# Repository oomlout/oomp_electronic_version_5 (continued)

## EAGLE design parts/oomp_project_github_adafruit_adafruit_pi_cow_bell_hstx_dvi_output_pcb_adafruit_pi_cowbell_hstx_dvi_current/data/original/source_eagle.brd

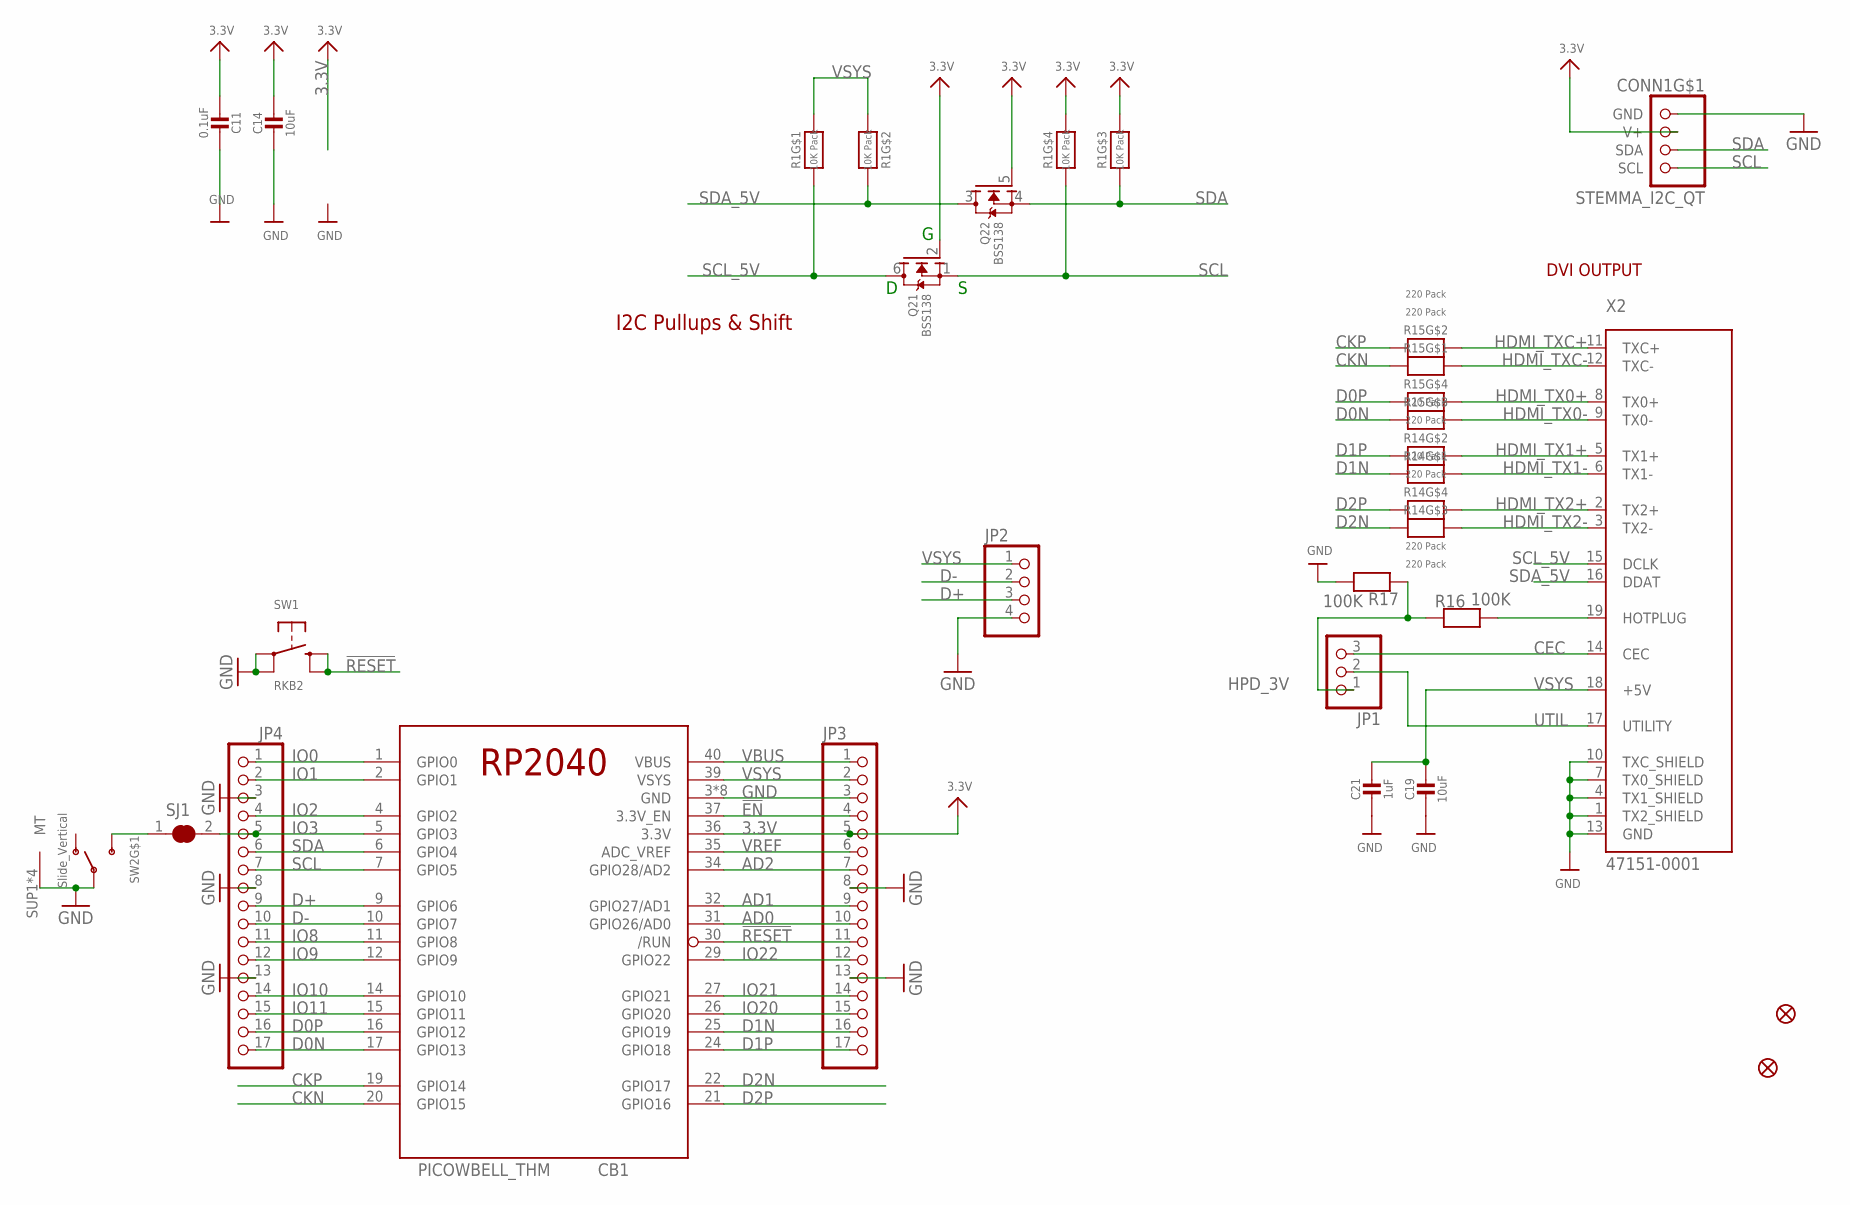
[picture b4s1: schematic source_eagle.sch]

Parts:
C11: 0.1uF; 0603-NO
C14, C19: 10uF; 0805-NO
C21: 1uF; 0603-NO
CB1: PICOWBELL_THM
CONN1: STEMMA_I2C_QT; JST_SH4
FID1, FID2: FIDUCIAL_1MM
JP1: HEADER-1X3ROUND; 1X03_ROUND
JP2: HEADER-1X4ROUND; 1X04_ROUND
JP3, JP4: HEADER-1X17; 1X17_ROUND70
Q2: BSS138; SOT363
R1: 10K Pack; RESPACK_4X0603
R14, R15: 220 Pack; RESPACK_4X0603
R16, R17: 100K; 0603-NO
SJ1: SOLDERJUMPER_CLOSED; SOLDERJUMPER_CLOSEDWIRE
SW1: RKB2; BTN_RKB2_4.6X2.8
SW2: Slide_Vertical; SPDT_SMT_SSSS811101
X2: 47151-0001; MINIHDMI_CNCTECH

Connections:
3.3V: C11.2, C14.1, CB1.36 (3.3V), CONN1.2 (V+), JP3.5, Q2.2 (G), Q2.5 (G), R1.5 (2), R1.6 (2)
!EN: CB1.37 (3.3V_EN), JP3.4
!RESET: CB1.30 (/RUN), JP3.11, SW1.B (S), SW1.B' (S1)
AD0: CB1.31 (GPIO26/AD0), JP3.10
AD1: CB1.32 (GPIO27/AD1), JP3.9
AD2: CB1.34 (GPIO28/AD2), JP3.7
CEC: JP1.3, X2.14 (CEC)
CKN: CB1.20 (GPIO15), R15.8 (2)
CKP: CB1.19 (GPIO14), R15.7 (2)
D0N: CB1.17 (GPIO13), JP4.17, R15.6 (2)
D0P: CB1.16 (GPIO12), JP4.16, R15.5 (2)
D1N: CB1.25 (GPIO19), JP3.16, R14.8 (2)
D1P: CB1.24 (GPIO18), JP3.17, R14.7 (2)
D2N: CB1.22 (GPIO17), R14.6 (2)
D2P: CB1.21 (GPIO16), R14.5 (2)
D+: CB1.9 (GPIO6), JP2.3, JP4.9
D-: CB1.10 (GPIO7), JP2.2, JP4.10
GND: C11.1, C14.2, C19.2, C21.2, CB1.3 (GND), CB1.8 (GND), CB1.13 (GND), CB1.18 (GND), CB1.23 (GND), CB1.28 (GND), CB1.33 (GND), CB1.38 (GND), CONN1.1 (GND), JP2.4, JP3.3, JP3.8, JP3.13, JP4.3, JP4.8, JP4.13, R17.2, SW1.A, SW1.A' (P1), SW2.B, SW2.SUP1 (MT), SW2.SUP2 (MT), SW2.SUP3 (MT), SW2.SUP4 (MT), X2.1 (TX2_SHIELD), X2.4 (TX1_SHIELD), X2.7 (TX0_SHIELD), X2.10 (TXC_SHIELD), X2.13 (GND), X2.MNT1 (GND), X2.MNT2 (GND), X2.MNT3 (GND), X2.MNT4 (GND)
HDMI_TX0+: R15.4 (1), X2.8 (TX0+)
HDMI_TX0-: R15.3 (1), X2.9 (TX0-)
HDMI_TX1+: R14.2 (1), X2.5 (TX1+)
HDMI_TX1-: R14.1, X2.6 (TX1-)
HDMI_TX2+: R14.4 (1), X2.2 (TX2+)
HDMI_TX2-: R14.3 (1), X2.3 (TX2-)
HDMI_TXC+: R15.2 (1), X2.11 (TXC+)
HDMI_TXC-: R15.1, X2.12 (TXC-)
HPD: R16.2, X2.19 (HOTPLUG)
HPD_3V: JP1.1, R16.1, R17.1
IO0: CB1.1 (GPIO0), JP4.1
IO1: CB1.2 (GPIO1), JP4.2
IO2: CB1.4 (GPIO2), JP4.4
IO3: CB1.5 (GPIO3), JP4.5, SJ1.2
IO8: CB1.11 (GPIO8), JP4.11
IO9: CB1.12 (GPIO9), JP4.12
IO10: CB1.14 (GPIO10), JP4.14
IO11: CB1.15 (GPIO11), JP4.15
IO20: CB1.26 (GPIO20), JP3.15
IO21: CB1.27 (GPIO21), JP3.14
IO22: CB1.29 (GPIO22), JP3.12
unnamed: SJ1.1, SW2.C (S)
SCL: CB1.7 (GPIO5), CONN1.4 (SCL), JP4.7, Q2.1 (S), R1.4 (1)
SCL_5V: Q2.6 (D), R1.8 (2), X2.15 (DCLK)
SDA: CB1.6 (GPIO4), CONN1.3 (SDA), JP4.6, Q2.4 (S), R1.3 (1)
SDA_5V: Q2.3 (D), R1.7 (2), X2.16 (DDAT)
UTIL: JP1.2, X2.17 (UTILITY)
VBUS: CB1.40 (VBUS), JP3.1
VREF: CB1.35 (ADC_VREF), JP3.6
VSYS: C19.1, C21.1, CB1.39 (VSYS), JP2.1, JP3.2, R1.1, R1.2 (1), X2.18 (+5V)

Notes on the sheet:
DVI OUTPUT
I2C Pullups & Shift

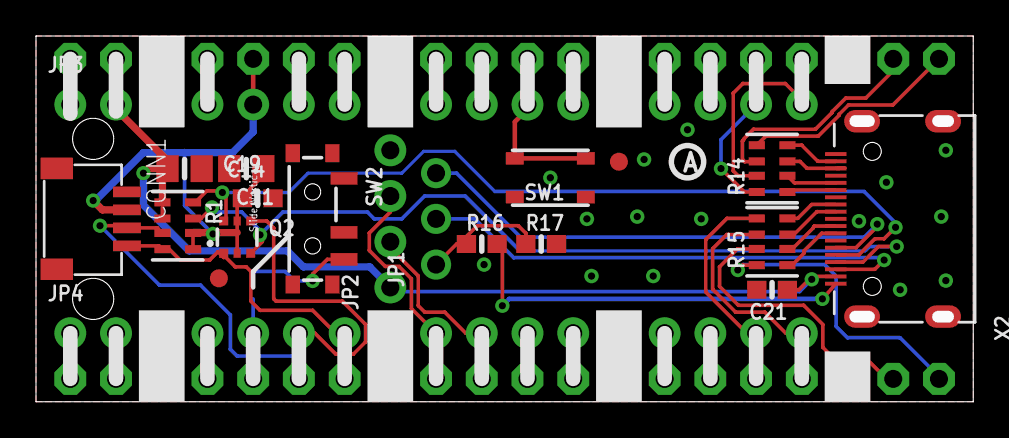
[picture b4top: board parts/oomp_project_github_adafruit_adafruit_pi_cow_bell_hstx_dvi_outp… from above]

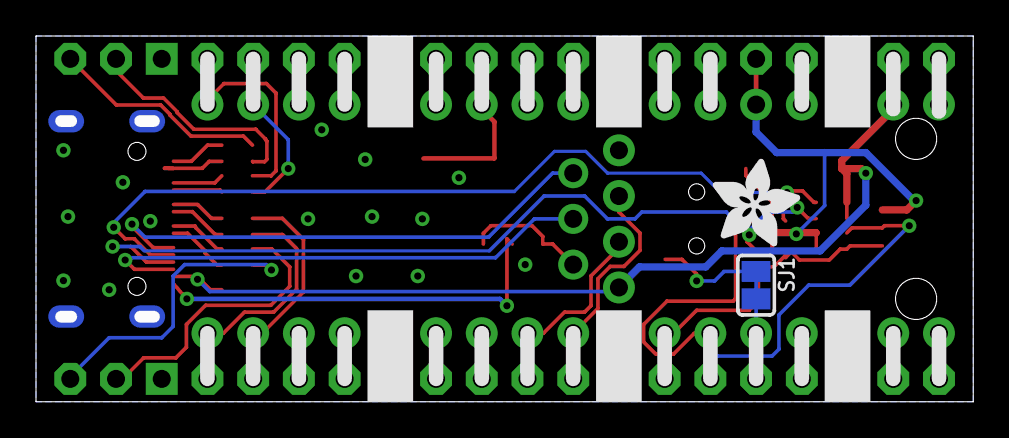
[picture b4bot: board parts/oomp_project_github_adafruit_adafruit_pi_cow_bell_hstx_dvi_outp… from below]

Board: 2 copper layers, 52.1 x 20.3 mm, 108 parts (44 on the bottom side), 48 nets.

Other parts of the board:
PLABEL109: PLABEL109
PLABEL110: PLABEL110
PLABEL111: PLABEL111
PLABEL112: PLABEL112
PLABEL113: PLABEL113
PLABEL114: PLABEL114
PLABEL115: PLABEL115
PLABEL116: PLABEL116
PLABEL117: PLABEL117
PLABEL118: PLABEL118
PLABEL119: PLABEL119
PLABEL120: PLABEL120
PLABEL121: PLABEL121
PLABEL122: PLABEL122
PLABEL123: PLABEL123
PLABEL124: PLABEL124
PLABEL125: PLABEL125
PLABEL126: PLABEL126
PLABEL127: PLABEL127
PLABEL128: PLABEL128
PLABEL129: PLABEL129
PLABEL130: PLABEL130
PLABEL131: PLABEL131
PLABEL132: PLABEL132
PLABEL133: PLABEL133
PLABEL134: PLABEL134
PLABEL135: PLABEL135
PLABEL136: PLABEL136
PLABEL137: PLABEL137
PLABEL138: PLABEL138
PLABEL139: PLABEL139
PLABEL140: PLABEL140
PLABEL141: PLABEL141
PLABEL142: PLABEL142
PLABEL143: PLABEL143
PLABEL144: PLABEL144
PLABEL145: PLABEL145
PLABEL146: PLABEL146
PLABEL147: PLABEL147
PLABEL148: PLABEL148
PLABEL149: PLABEL149
PLABEL150: PLABEL150
PLABEL151: PLABEL151
PLABEL152: PLABEL152
PLABEL154: PLABEL154
PLABEL155: PLABEL155
PLABEL156: PLABEL156
PLABEL157: PLABEL157
PLABEL158: PLABEL158
PLABEL159: PLABEL159
PLABEL160: PLABEL160
PLABEL161: PLABEL161
PLABEL162: PLABEL162
PLABEL163: PLABEL163
PLABEL164: PLABEL164
PLABEL165: PLABEL165
PLABEL166: PLABEL166
PLABEL167: PLABEL167
PLABEL168: PLABEL168
PLABEL169: PLABEL169
PLABEL170: PLABEL170
PLABEL171: PLABEL171
PLABEL172: PLABEL172
PLABEL173: PLABEL173
PLABEL174: PLABEL174
PLABEL175: PLABEL175
PLABEL176: PLABEL176
PLABEL177: PLABEL177
PLABEL178: PLABEL178
PLABEL179: PLABEL179
PLABEL180: PLABEL180
PLABEL181: PLABEL181
PLABEL182: PLABEL182
PLABEL183: PLABEL183
PLABEL184: PLABEL184
PLABEL185: PLABEL185
PLABEL186: PLABEL186
PLABEL187: PLABEL187
PLABEL188: PLABEL188
PLABEL189: PLABEL189
PLABEL190: PLABEL190
PLABEL191: PLABEL191
PLABEL192: PLABEL192
PLABEL193: PLABEL193
U$1: ADAFRUIT_5MM
U$10: PCBFEAT-REV-040

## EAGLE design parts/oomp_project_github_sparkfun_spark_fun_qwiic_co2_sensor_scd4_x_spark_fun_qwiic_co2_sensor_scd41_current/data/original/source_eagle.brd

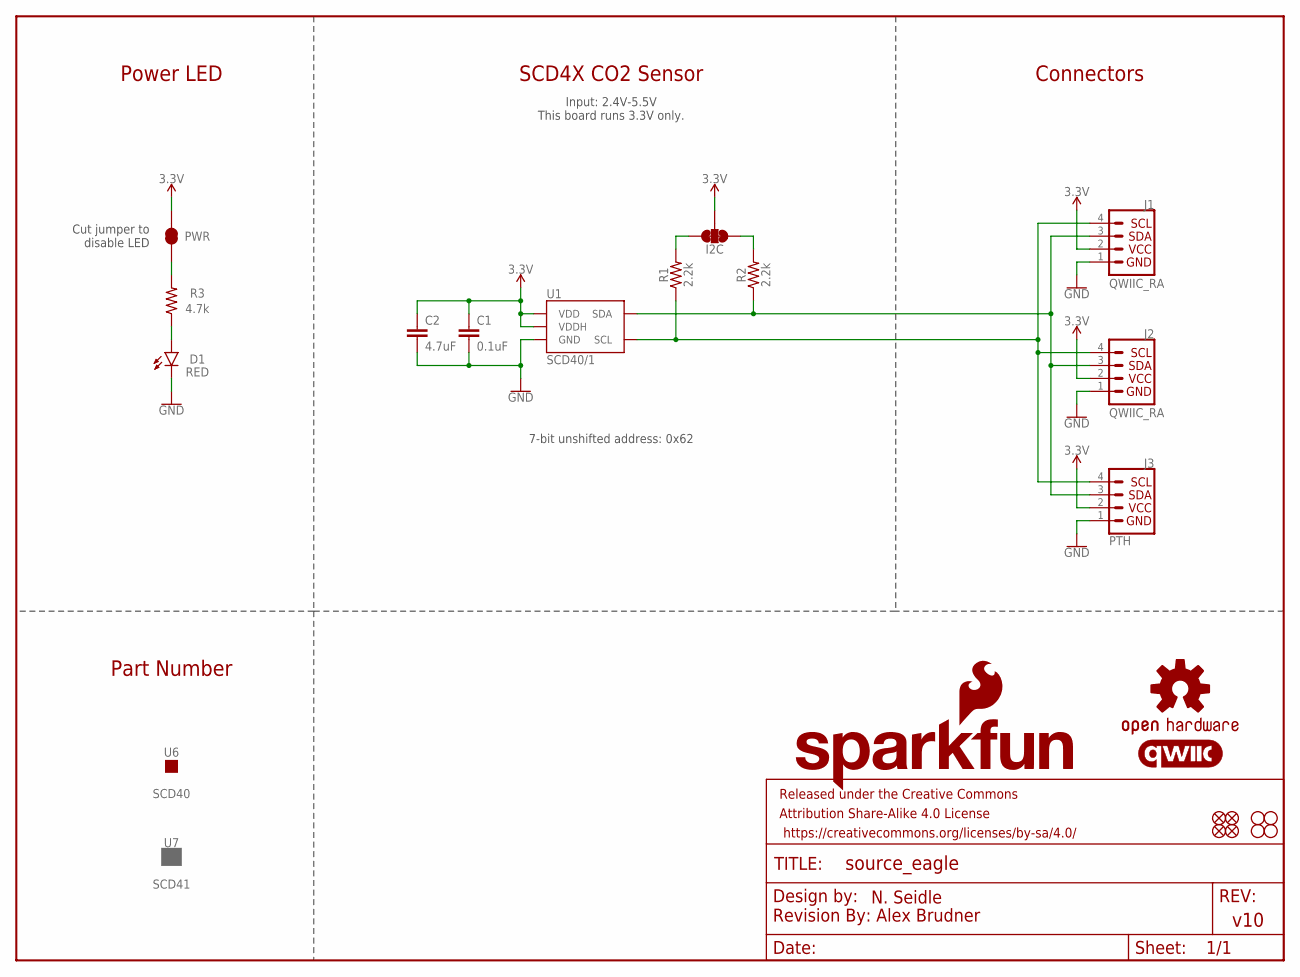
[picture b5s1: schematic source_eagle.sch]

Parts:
C1: 0.1uF; 0603
C2: 4.7uF; 0603
D1: RED; LED-0603
FD1, FD2, FD3, FD4: FIDUCIALUFIDUCIAL; FIDUCIAL-MICRO
FRAME1: FRAME-LETTER; CREATIVE_COMMONS
H1, H2, H3, H4: STAND-OFF
I2C: I2C; SMT-JUMPER_3_2-NC_TRACE_SILK
J1, J2: QWIIC_RA; JST04_1MM_RA
J3: PTH; 1X04_NO_SILK
LOGO1: QWIIC_LOGO_CONNECTOR; QWIIC_5.5MM
LOGO2: OSHW-LOGOS; OSHW-LOGO-S
LOGO3: SFE_LOGO_NAME_FLAMEBLANK; BLANK
PWR: PWR; SMT-JUMPER_2_NC_TRACE_SILK
R1, R2: 2.2k; 0603
R3: 4.7k; 0603
U1: SCD40/1; SCD4X
U6: SCD40; PRODUCT_IDENT_NO_NO-SILK
U7: SCD41; PRODUCT_IDENT_PASTE_NO-SILK

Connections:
3.3V: C1.1, C2.1, I2C.2, J1.2, J2.2, J3.2, PWR.2, U1.7 (VDD), U1.19 (VDDH)
GND: C1.2, C2.2, D1.C, J1.1, J2.1, J3.1, U1.6 (GND), U1.20 (GND), U1.CP (GND)
unnamed: I2C.1, R2.2
unnamed: I2C.3, R1.2
unnamed: PWR.1, R3.2
unnamed: D1.A, R3.1
SCL: J1.4, J2.4, J3.4, R1.1, U1.9 (SCL)
SDA: J1.3, J2.3, J3.3, R2.1, U1.10 (SDA)

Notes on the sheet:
Cut jumper to disable LED
SCD4X CO2 Sensor
Power LED
Connectors
Part Number
Input: 2.4V-5.5V This board runs 3.3V only.
7-bit unshifted address: 0x62

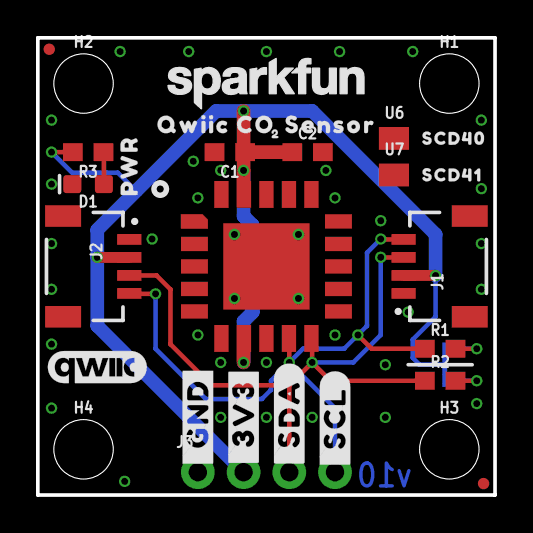
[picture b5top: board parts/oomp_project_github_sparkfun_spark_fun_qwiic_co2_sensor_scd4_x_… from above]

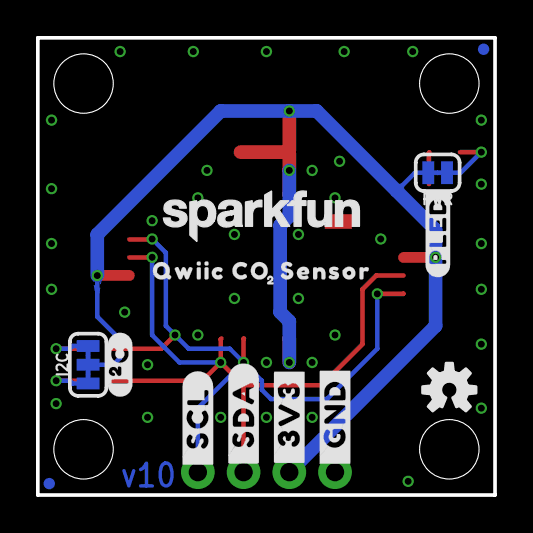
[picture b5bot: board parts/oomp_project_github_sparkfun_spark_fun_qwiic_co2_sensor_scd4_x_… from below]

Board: 2 copper layers, 25.4 x 25.4 mm, 49 parts (16 on the bottom side), 8 nets.

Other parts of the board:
U$1, U$18: #_GND#14
U$2, U$19: #_3V3#15
U$3, U$20: #_SDA#15
U$4, U$21: #_SCL#16
U$5, U$12: SFE_LOGO_NAME_.1
U$6: SCD414140404021
U$7: SCD40414140404022
U$8, U$13: QWIIC_CO0
U$9, U$14: SENSOR0
U$10, U$15: 20
U$11: SFE_LOGO_FLAME_STOP_.1
U$16: #PLED#21
U$17: #I�C#0
U$22: ORDERING_INSTRUCTIONS
U$23: PWR0

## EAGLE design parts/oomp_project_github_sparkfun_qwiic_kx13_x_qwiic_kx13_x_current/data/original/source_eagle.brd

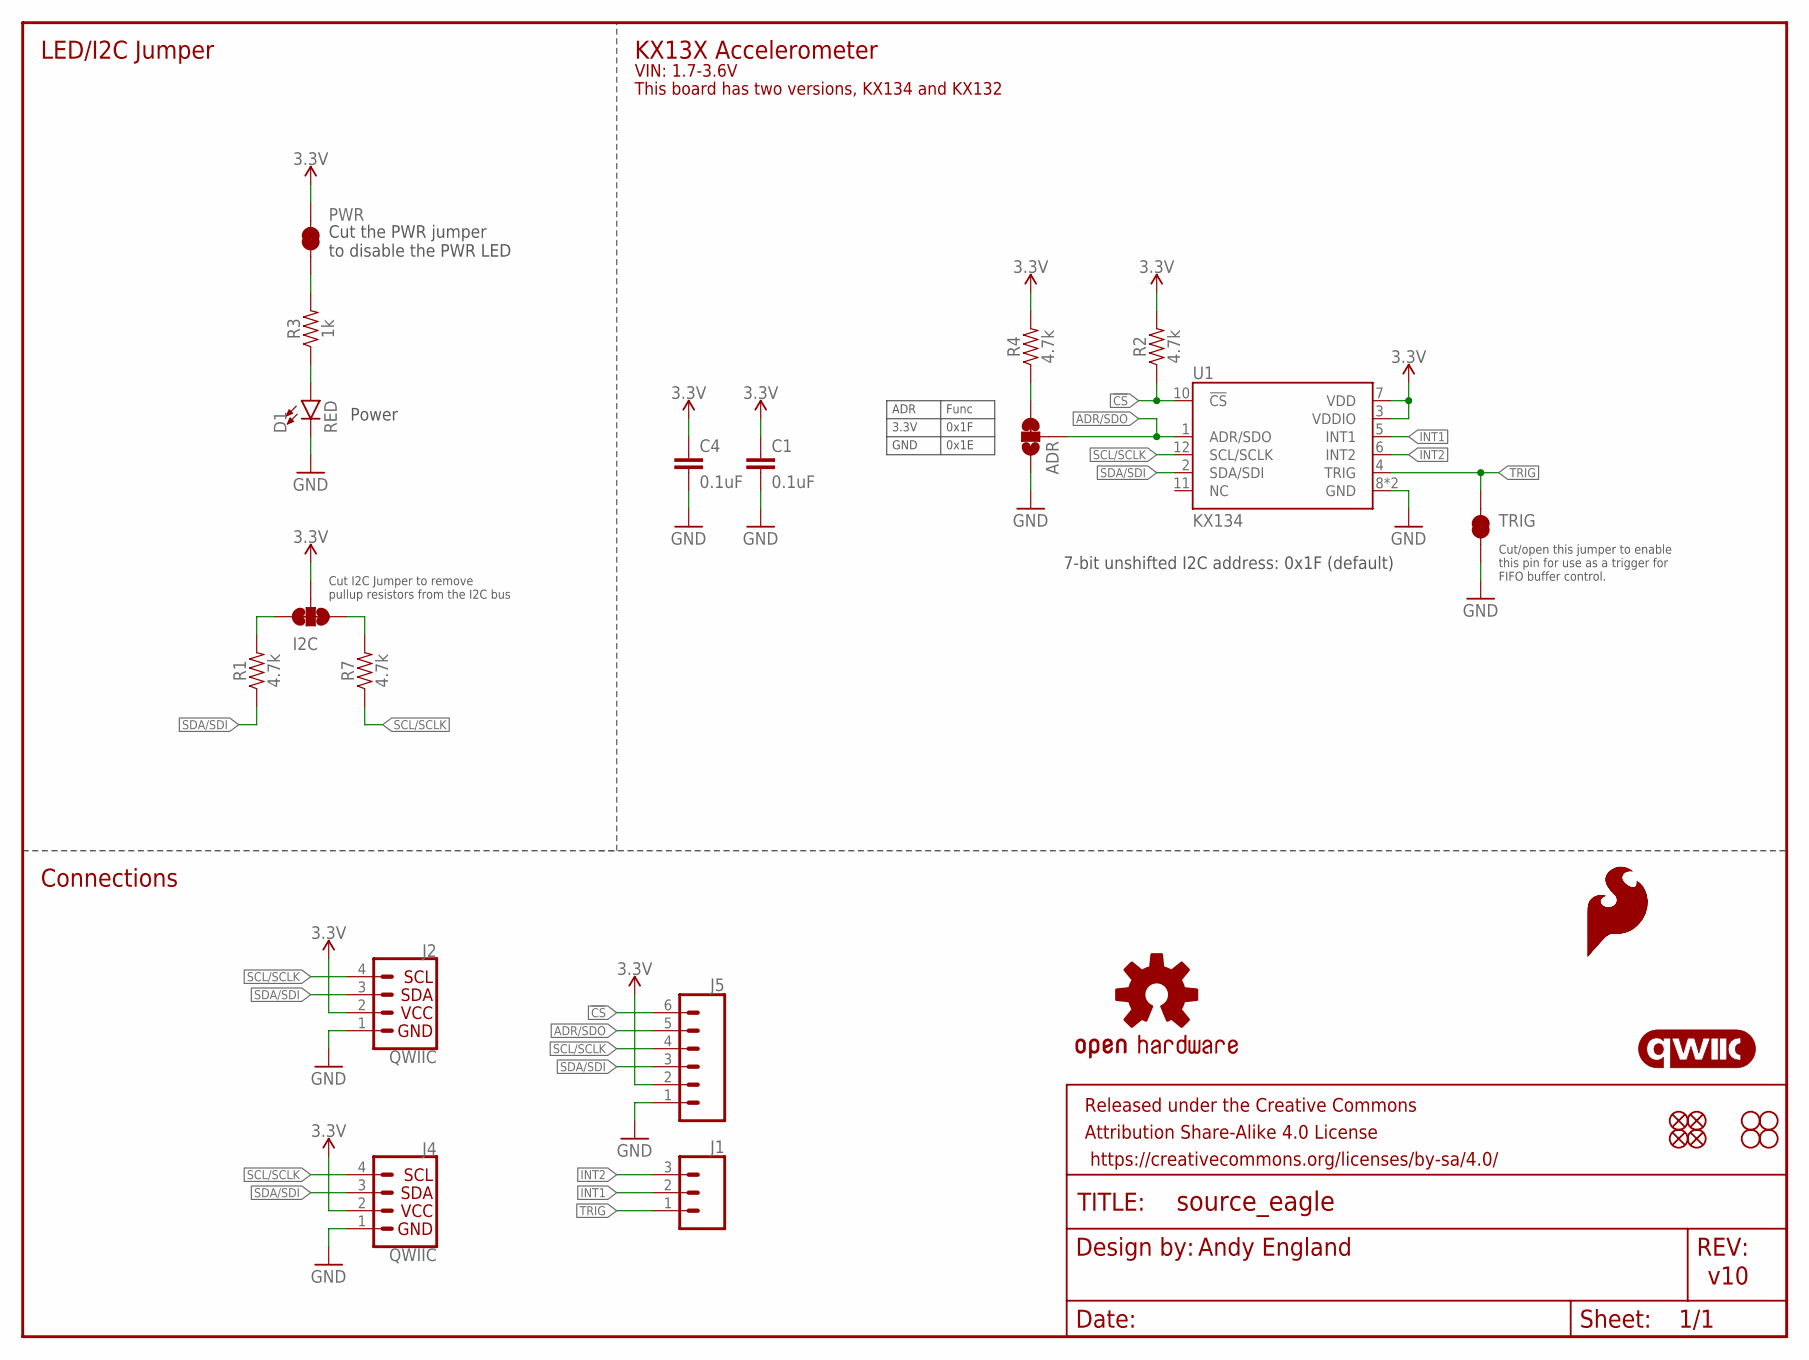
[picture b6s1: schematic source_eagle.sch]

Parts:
ADR: JUMPER-SMT_3_1-NC_TRACE_SILK; SMT-JUMPER_3_1-NC_TRACE_SILK
C1, C4: 0.1uF; 0603
D1: RED; LED-0603
FRAME1: FRAME-LETTER; CREATIVE_COMMONS
I2C: JUMPER-SMT_3_2-NC_TRACE_SILK; SMT-JUMPER_3_2-NC_TRACE_SILK
J1: CONN_031X03_NO_SILK; 1X03_NO_SILK
J2, J4: QWIIC; JST04_1MM_RA
J5: CONN_06NO_SILK_NO_POP; 1X06_NO_SILK
JP1, JP2, JP5, JP6: FIDUCIALUFIDUCIAL; MICRO-FIDUCIAL
JP3, JP4, JP7, JP8: STAND-OFF
LOGO1, LOGO2: SFE_LOGO_FLAME.1_INCH; SFE_LOGO_FLAME_.1
LOGO3: QWIIC_LOGO_4MM; QWIIC_4MM
LOGO5: OSHW-LOGOS; OSHW-LOGO-S
PWR: JUMPER-SMT_2_NC_TRACE_SILK; SMT-JUMPER_2_NC_TRACE_SILK
R1, R2, R4, R7: 4.7k; 0603
R3: 1k; 0603
TRIG: JUMPER-SMT_2_NC_TRACE_SILK; SMT-JUMPER_2_NC_TRACE_SILK
U1: KX134; KX13X

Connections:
3.3V: C1.1, C4.1, I2C.2, J2.2, J4.2, J5.2, PWR.2, R2.2, R4.2, U1.3 (VDDIO), U1.7 (VDD)
!CS: J5.6, R2.1, U1.10 (!CS)
ADR/SDO: ADR.2, J5.5, U1.1 (ADR/SDO)
GND: ADR.1, C1.2, C4.2, D1.C, J2.1, J4.1, J5.1, TRIG.2, U1.8 (GND), U1.9 (GND)
INT1: J1.2, U1.5 (INT1)
INT2: J1.3, U1.6 (INT2)
unnamed: PWR.1, R3.2
unnamed: I2C.3, R1.2
unnamed: D1.A, R3.1
unnamed: I2C.1, R7.2
unnamed: ADR.3, R4.1
SCL/SCLK: J2.4, J4.4, J5.4, R7.1, U1.12 (SCL/SCLK)
SDA/SDI: J2.3, J4.3, J5.3, R1.1, U1.2 (SDA/SDI)
TRIG: J1.1, TRIG.1, U1.4 (TRIG)

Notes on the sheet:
v10
7-bit unshifted I2C address: 0x1F (default)
Power
Cut the PWR jumper to disable the PWR LED
Andy England
Cut I2C Jumper to remove pullup resistors from the I2C bus
Cut/open this jumper to enable this pin for use as a trigger for FIFO buffer control.
ADR
Func
3.3V
0x1F
0x1E
GND
KX13X Accelerometer
VIN: 1.7-3.6V
LED/I2C Jumper
Connections
This board has two versions, KX134 and KX132

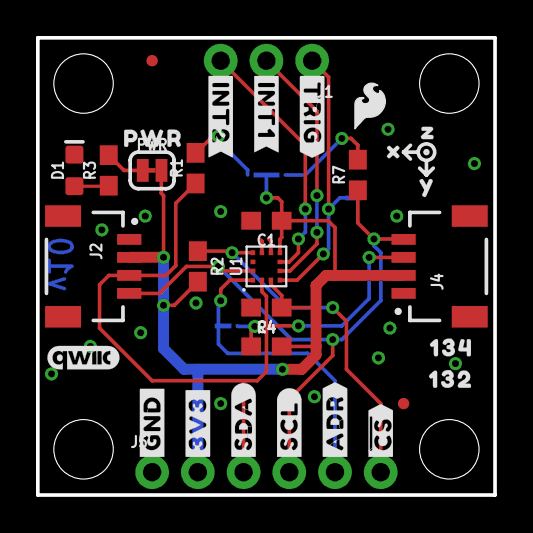
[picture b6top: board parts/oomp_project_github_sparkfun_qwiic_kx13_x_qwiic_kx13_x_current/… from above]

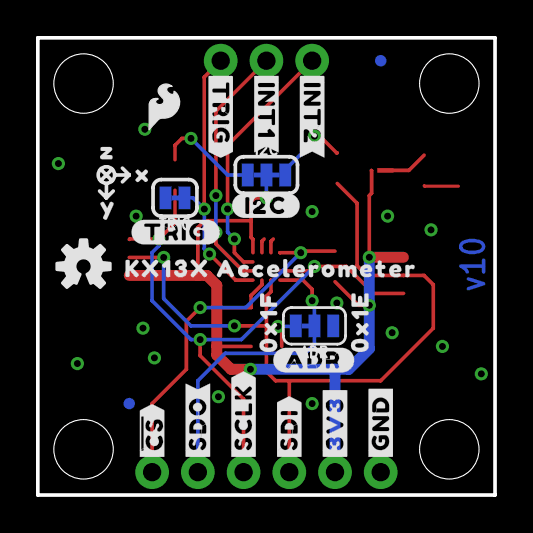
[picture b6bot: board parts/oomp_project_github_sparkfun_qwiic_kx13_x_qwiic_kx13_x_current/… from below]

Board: 2 copper layers, 25.4 x 25.4 mm, 63 parts (25 on the bottom side), 14 nets.

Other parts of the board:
U$1, U$28: X0
U$2: #SCL#0
U$3: #SDA#0
U$4, U$5: #3V3#0
U$6, U$7: #GND#0
U$8, U$9: ##CS##0
U$10: #ADR#0
U$11, U$15: #TRIG#0
U$12, U$13: #INT1#0
U$14: 0X1E0
U$17: #TRIG#2
U$18, U$19: #INT2#0
U$20: #ADR#3
U$21, U$29: Y0
U$22: #I2C#0
U$23: 0X1F0
U$24: #SDI#0
U$25: #SCLK#0
U$26: #SDO#0
U$27: KX13X_ACCELEROMETER14
U$30, U$32: Z0
U$31: PWR0
U$33: 1320
U$34: 1340

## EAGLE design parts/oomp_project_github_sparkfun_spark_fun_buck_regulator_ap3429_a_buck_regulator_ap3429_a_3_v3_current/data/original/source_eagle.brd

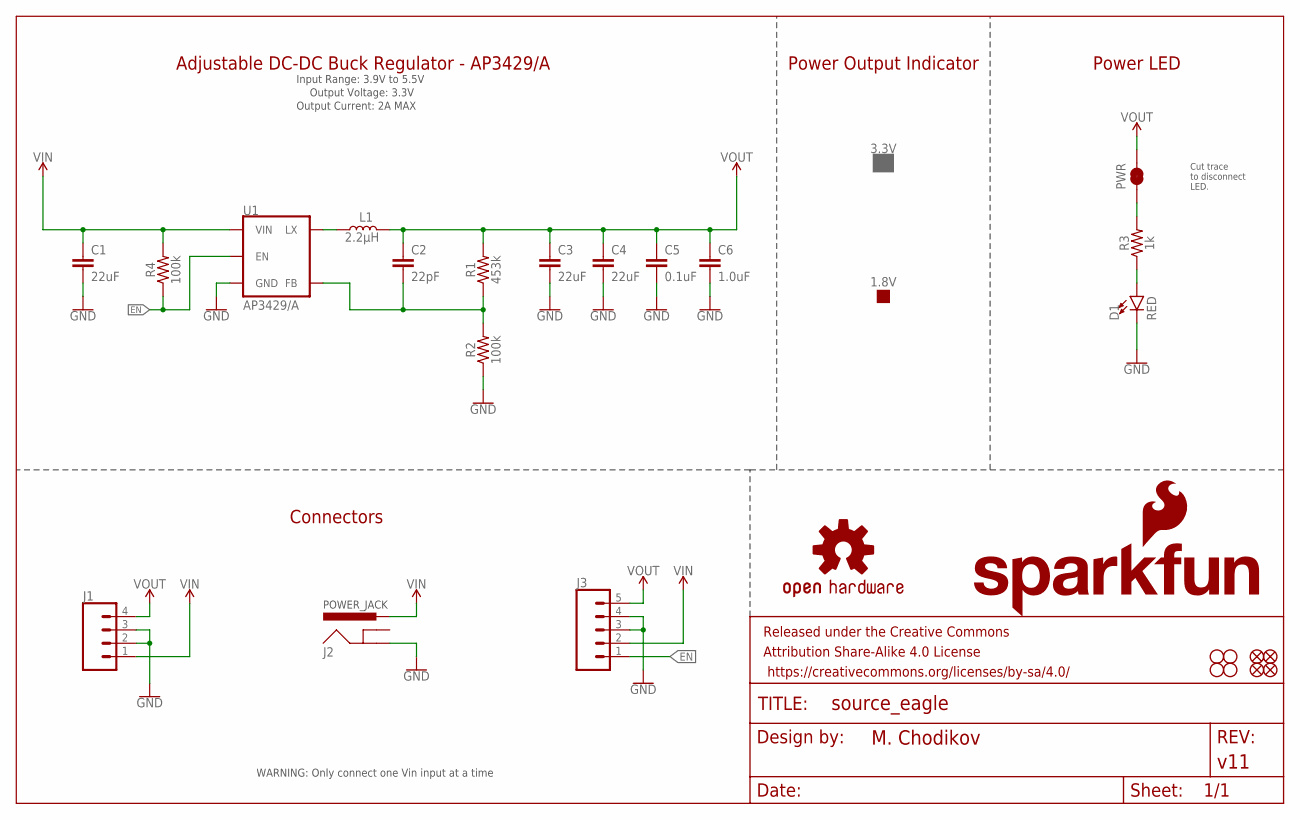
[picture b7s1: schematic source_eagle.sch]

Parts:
1.8V: PROD_ID_NO-PASTE_NO_SILK; PRODUCT_IDENT_NO_NO-SILK
3.3V: PROD_ID_PASTE_NO-SILK; PRODUCT_IDENT_PASTE_NO-SILK
C1, C3, C4: 22uF; 0805
C2: 22pF; 0402-TIGHT
C5: 0.1uF; 0603
C6: 1.0uF; 0603
D1: RED; LED-0603
FD1, FD2, FD3, FD4: FIDUCIALUFIDUCIAL; FIDUCIAL-MICRO
FRAME1: FRAME-LEDGER; CREATIVE_COMMONS
H1, H2, H3, H4: STAND-OFFTIGHT; STAND-OFF-TIGHT
J1: Screw Terminal; SCREWTERMINAL-3.5MM-4
J2: POWER_JACKPOWER_JACK_SLOT_COMBO; POWER_JACK_PTH_SLOT_BOTH
J3: Breakout Headers; 1X05_NO_SILK
L1: 2.2μH; INDUCTOR_4X4MM
LOGO1: OSHW-LOGOS; OSHW-LOGO-S
LOGO2: SFE_LOGO_NAME.1_INCH; SFE_LOGO_NAME_.1
LOGO3: SFE_LOGO_FLAME.1_INCH; SFE_LOGO_FLAME_.1
PWR: JUMPER-SMT_2_NC_TRACE_SILK; SMT-JUMPER_2_NC_TRACE_SILK
R1: 453k; 0603
R2, R4: 100k; 0603
R3: 1k; 0603
U1: AP3429/A; SOT23-5

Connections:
EN: J3.1, R4.1, U1.1 (EN)
GND: C1.2, C3.2, C4.2, C5.2, C6.2, D1.C, J1.2, J1.3, J2.GND, J3.3, J3.4, R2.1, U1.2 (GND)
unnamed: L1.P$1 (1), U1.3 (LX)
unnamed: C2.2, R1.1, R2.2, U1.5 (FB)
unnamed: PWR.1, R3.2
unnamed: D1.A, R3.1
VIN: C1.1, J1.1, J2.PWR, J3.2, R4.2, U1.4 (VIN)
VOUT: C2.1, C3.1, C4.1, C5.1, C6.1, J1.4, J3.5, L1.P$2 (2), PWR.2, R1.2

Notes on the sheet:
Input Range: 3.9V to 5.5V
Adjustable DC-DC Buck Regulator - AP3429/A
Power LED
Connectors
POWER_JACK
Output Current: 2A MAX
WARNING: Only connect one Vin input at a time
Power Output Indicator
Cut trace to disconnect LED.
Output Voltage: 3.3V

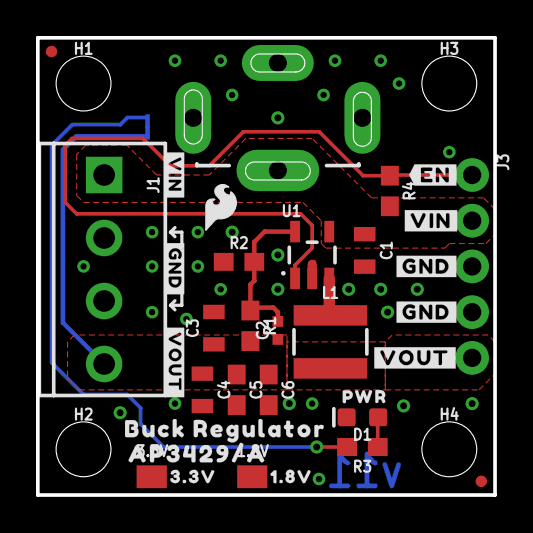
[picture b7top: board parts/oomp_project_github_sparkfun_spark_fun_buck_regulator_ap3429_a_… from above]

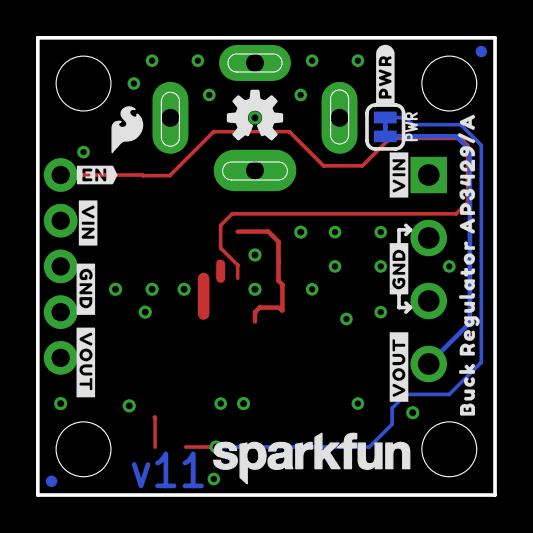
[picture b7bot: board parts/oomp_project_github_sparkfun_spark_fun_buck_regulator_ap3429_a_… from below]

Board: 2 copper layers, 25.4 x 25.4 mm, 55 parts (15 on the bottom side), 8 nets.

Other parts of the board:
U$1: SFE_LOGO_FLAME_.1
U$2: BUCK_REGULATOR24
U$3: AP3429#A25
U$4: #VOUT#3431
U$5, U$6: #GND#3432
U$7: #VIN#3433
U$8, U$10: #GND#3446
U$9, U$15: #VIN#3445
U$11, U$13: #VOUT#3447
U$12: #EN#3448
U$14: #PWR#3451
U$16: BUCK_REGULATOR_AP3429#A3453
U$17: ORDERING_INSTRUCTIONS
U$19: 1#8V3441
U$20: PWR3441
U$21: #VOUT#3437
U$22: #VIN#3438
U$23: 3#3V3441
U$24: #GND#3439
U$25: #EN#3443
